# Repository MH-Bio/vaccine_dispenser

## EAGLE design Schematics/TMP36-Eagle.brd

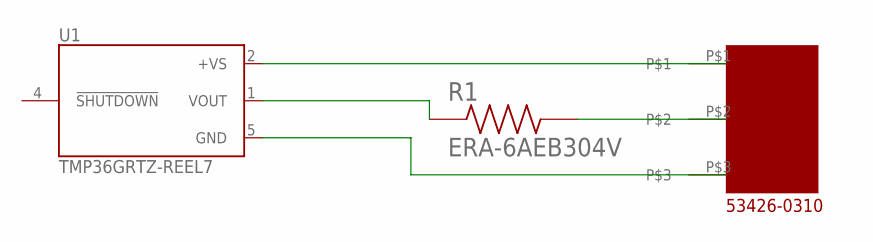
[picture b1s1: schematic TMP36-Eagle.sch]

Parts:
R1: ERA-6AEB304V; RESC2012X60N
U1: TMP36GRTZ-REEL7; SOT95P280X145-5N
U$6: 53426-0310

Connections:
unnamed: R1.1, U1.1 (VOUT)
unnamed: U1.2 (+VS), U$6.P$1
unnamed: U1.5 (GND), U$6.P$3
unnamed: R1.2, U$6.P$2

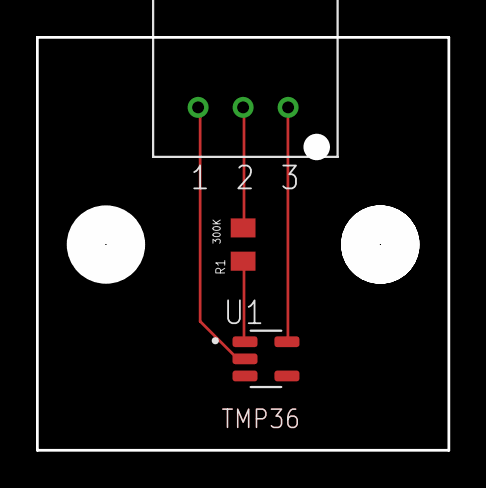
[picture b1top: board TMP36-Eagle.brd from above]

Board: 2 copper layers, 22.8 x 22.8 mm, 3 parts (0 on the bottom side), 4 nets.

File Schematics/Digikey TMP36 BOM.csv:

Manufacturer Part Number,Manufacturer,Digi-Key Part Number,Customer Reference,Reference Designator,Packaging,Part Status,Quantity,Unit Price,Extended Price,Quantity Available,Mfg Std Lead Time,Description,RoHS Status,Lead Free Status,REACH Status,URL
TMP36GRTZ-REEL7,Analog Devices Inc.,TMP36GRTZ-REEL7CT-ND,,,Cut Tape (CT),Active,1,1.75,$1.75 ,10033,8 Weeks,SENSOR ANALOG -40C-125C SOT23-5,ROHS3 Compliant,Lead free,REACH Unaffected,https://www.digikey.com/product-detail/en/analog-devices-inc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
ERA-6AEB304V,Panasonic Electronic Components,P300KDACT-ND,,,Cut Tape (CT),Active,1,0.36,$0.36 ,62660,12 Weeks,RES 300K OHM 0.1% 1/8W 0805,ROHS3 Compliant,Lead free,REACH Unaffected,https://www.digikey.com/product-detail/en/panasonic-electron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
534260310,Molex,WM7586-ND,,,Tray,Active,1,0.43,$0.43 ,7724,15 Weeks,CONN HEADER R/A 3POS 2.5MM,ROHS3 Compliant,Lead free,REACH Unaffected,https://www.digikey.com/products/en?keywords=WM7586-ND

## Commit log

2023-05-29 Added Arduino Libraries Directory
